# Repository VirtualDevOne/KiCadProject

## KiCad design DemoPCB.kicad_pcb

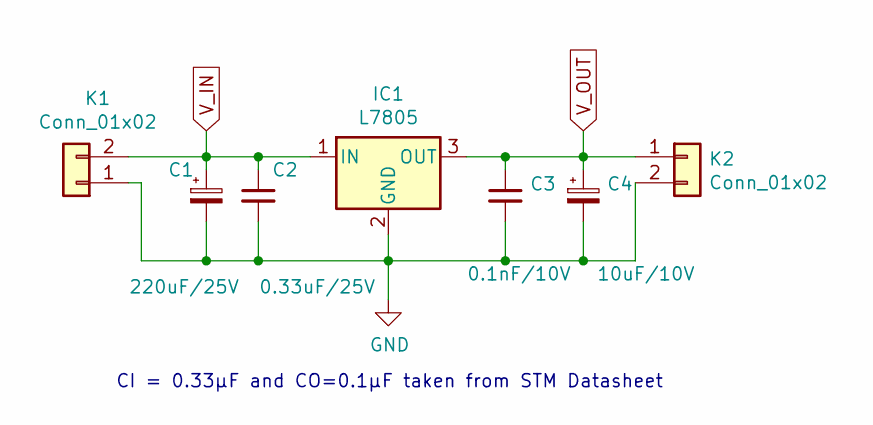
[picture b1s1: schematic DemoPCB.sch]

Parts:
C1: 220uF/25V; CP_Radial_D6.3mm_P2.50mm
C2: 0.33uF/25V; C_Rect_L7.2mm_W2.5mm_P5.00mm_FKS2_FKP2_MKS2_MKP2
C3: 0.1nF/10V; C_Rect_L7.2mm_W2.5mm_P5.00mm_FKS2_FKP2_MKS2_MKP2
C4: 10uF/10V; CP_Radial_D5.0mm_P2.00mm
IC1: L7805; TO-220-3_Horizontal_TabDown
K1, K2: Conn_01x02; PinHeader_1x02_P2.54mm_Vertical

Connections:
GND: C1.2, C2.2, C3.2, C4.2, IC1.2 (GND), K1.1, K2.2
V_IN: C1.1, C2.1, IC1.1 (IN), K1.2
V_OUT: C3.1, C4.1, IC1.3 (OUT), K2.1

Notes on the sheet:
CI = 0.33µF and CO=0.1µF taken from STM Datasheet

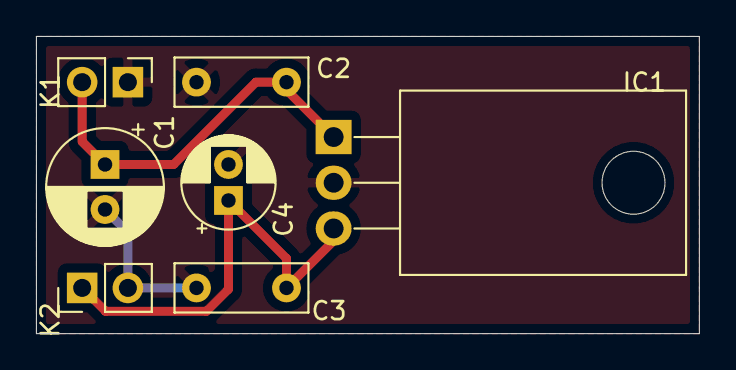
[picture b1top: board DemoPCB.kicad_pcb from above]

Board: 2 copper layers, 36.8 x 16.5 mm, 7 parts (0 on the bottom side), 3 nets.

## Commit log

2021-12-09 first commit
    our first one
2021-12-09 second fix
    fixed a few things
2021-12-09 switch back
    switch back
2021-12-09 first final release
2021-12-09 Changed a label
    better placement
